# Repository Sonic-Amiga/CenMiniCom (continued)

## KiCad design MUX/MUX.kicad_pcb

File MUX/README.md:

# MUX board replica

# Modifications list.

1. SN74199 is replaced by SN74LS273

2. SN74LS154 can be replaced by russian КР1533ИД3 in a narrow package, extra row of pins provided

3. Added jumper blocks for easy switch between original Centurion and standard RS-232 output pinouts.

See git log for more verbose history

Russian characters in this file are using UTF-8 character set.

|Original   |Replacement        |Notes					|
|-----------|-------------------|---------------------------------------|
|74LS00		|К555ЛА3			|					|
|74LS02		|К555ЛЕ1			|					|
|74LS04		|К555ЛН1			|					|
|74LS08		|К555ЛИ1			|
|74LS10		|К555ЛА4			|					|
|74LS20		|К555ЛА1			|					|
|74LS30		|К555ЛА2			|					|
|SN7425		|155ЛЕ3				|
|74LS37		|К555ЛА12			|					|
|74LS38		|К555ЛА13			|					|
|74LS42		|К555ИД6			|
|74LS74		|К555ТМ2			|					|
|74LS75		|555TM7				|
|74LS85		|555СП1				|
|74LS148	|КМ555ИВ1			|
|74LS151	|К555КП7			|					|
|74LS154	|К155ИД3, К1533ИД3	| К1533 series uses narrow DIP package	|
|74LS161	|К555ИЕ10			|
|74LS195	|					|
|74LS240	|К555АП3			|					|
|74LS273	|К555ИР35			|
|74LS367	|КР571ХЛ5			|
|74LS393	|К555ИЕ19			|
|SN75150	|170АП2				|
|SN75154	|170УП2				|

# Contacts

Please direct all questions to pavel_fedin@mail.ru

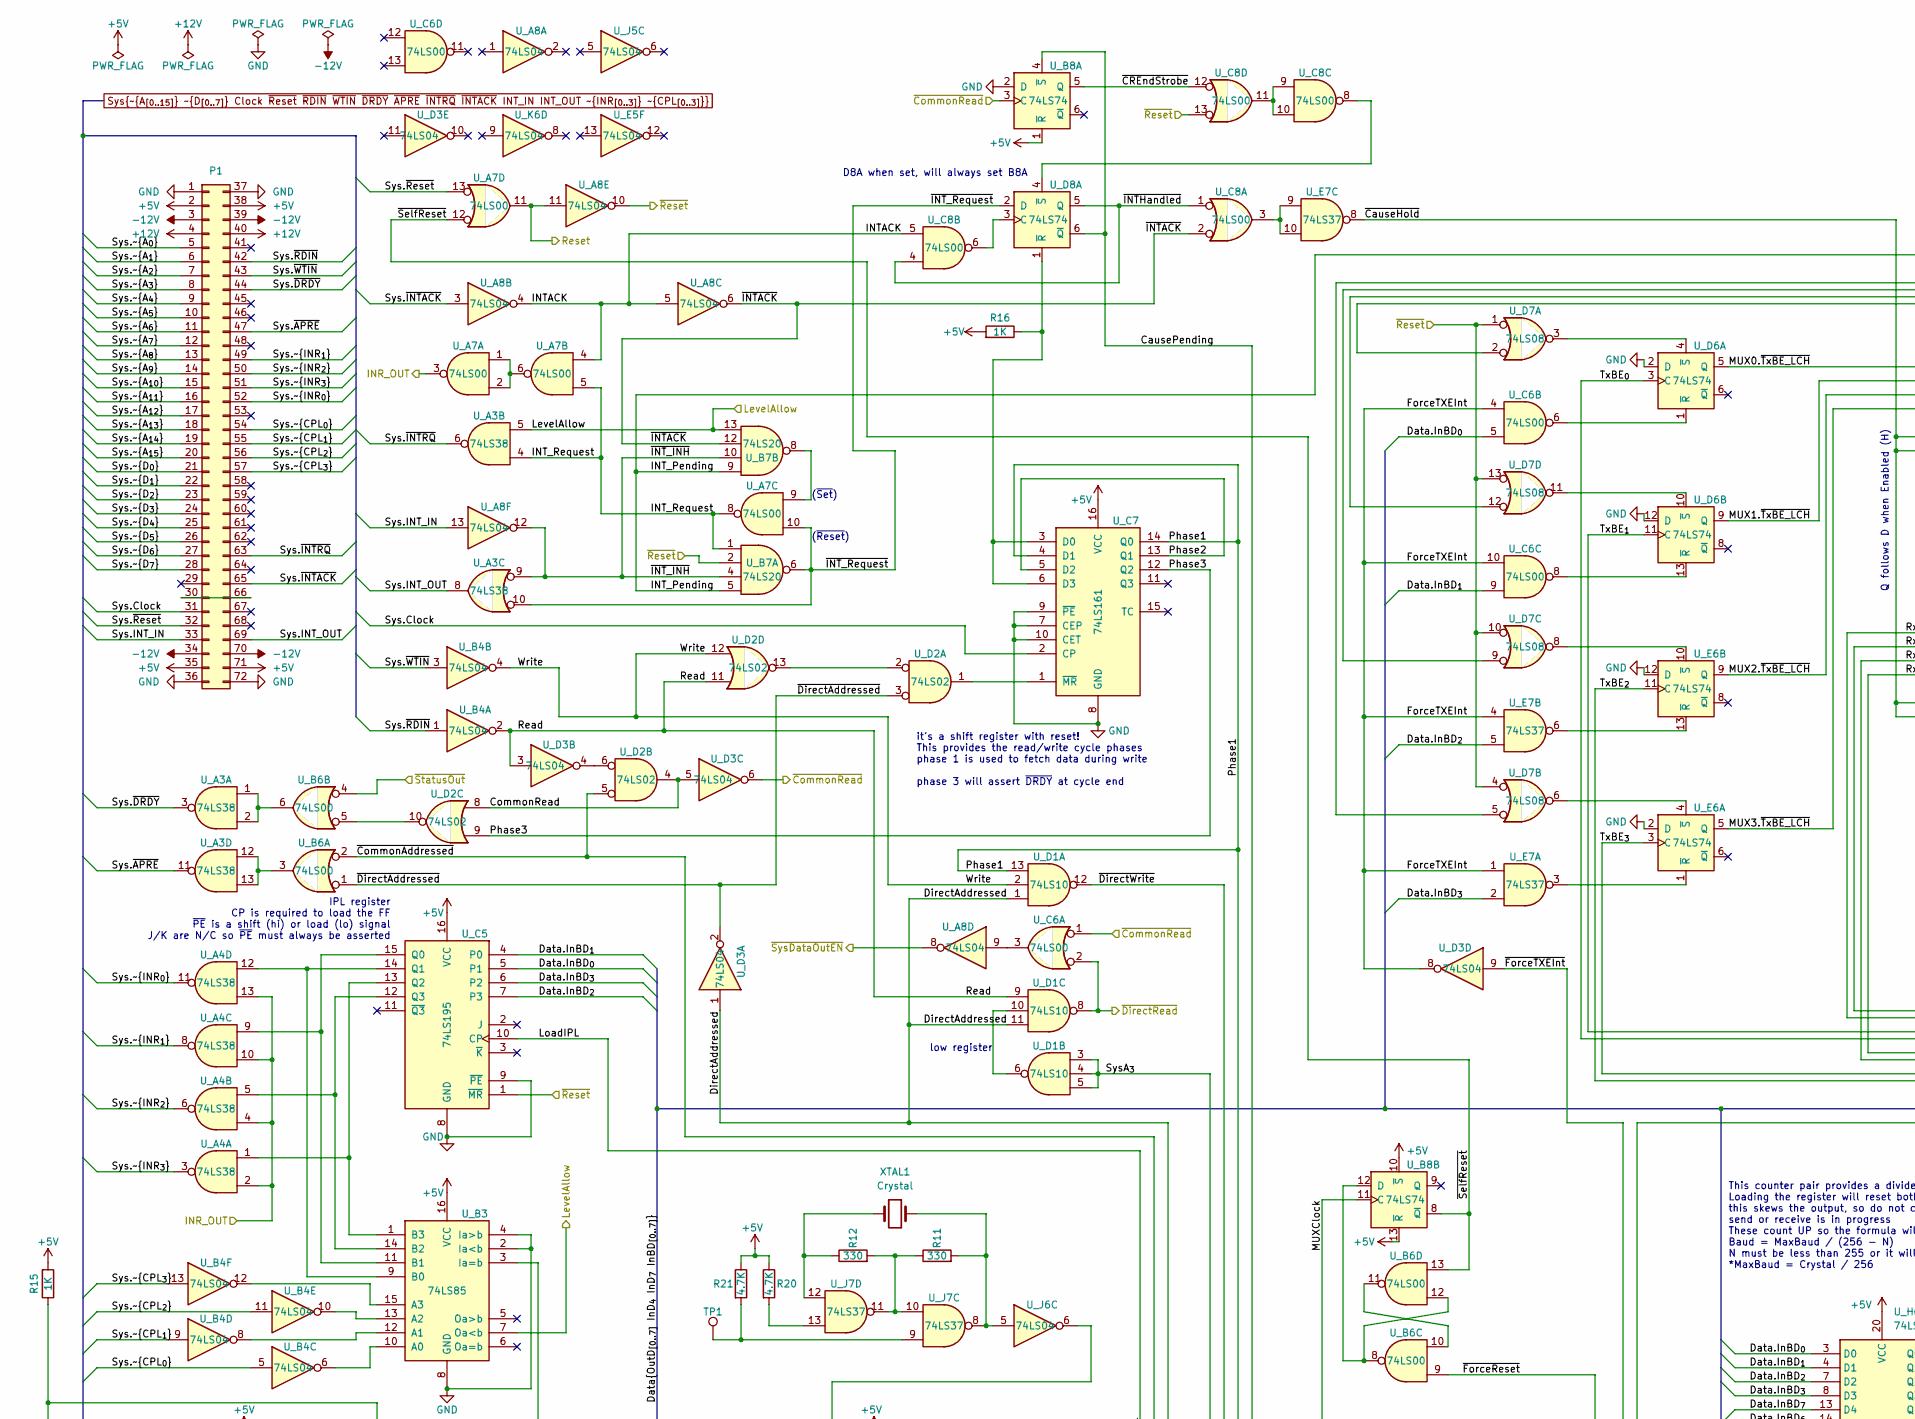
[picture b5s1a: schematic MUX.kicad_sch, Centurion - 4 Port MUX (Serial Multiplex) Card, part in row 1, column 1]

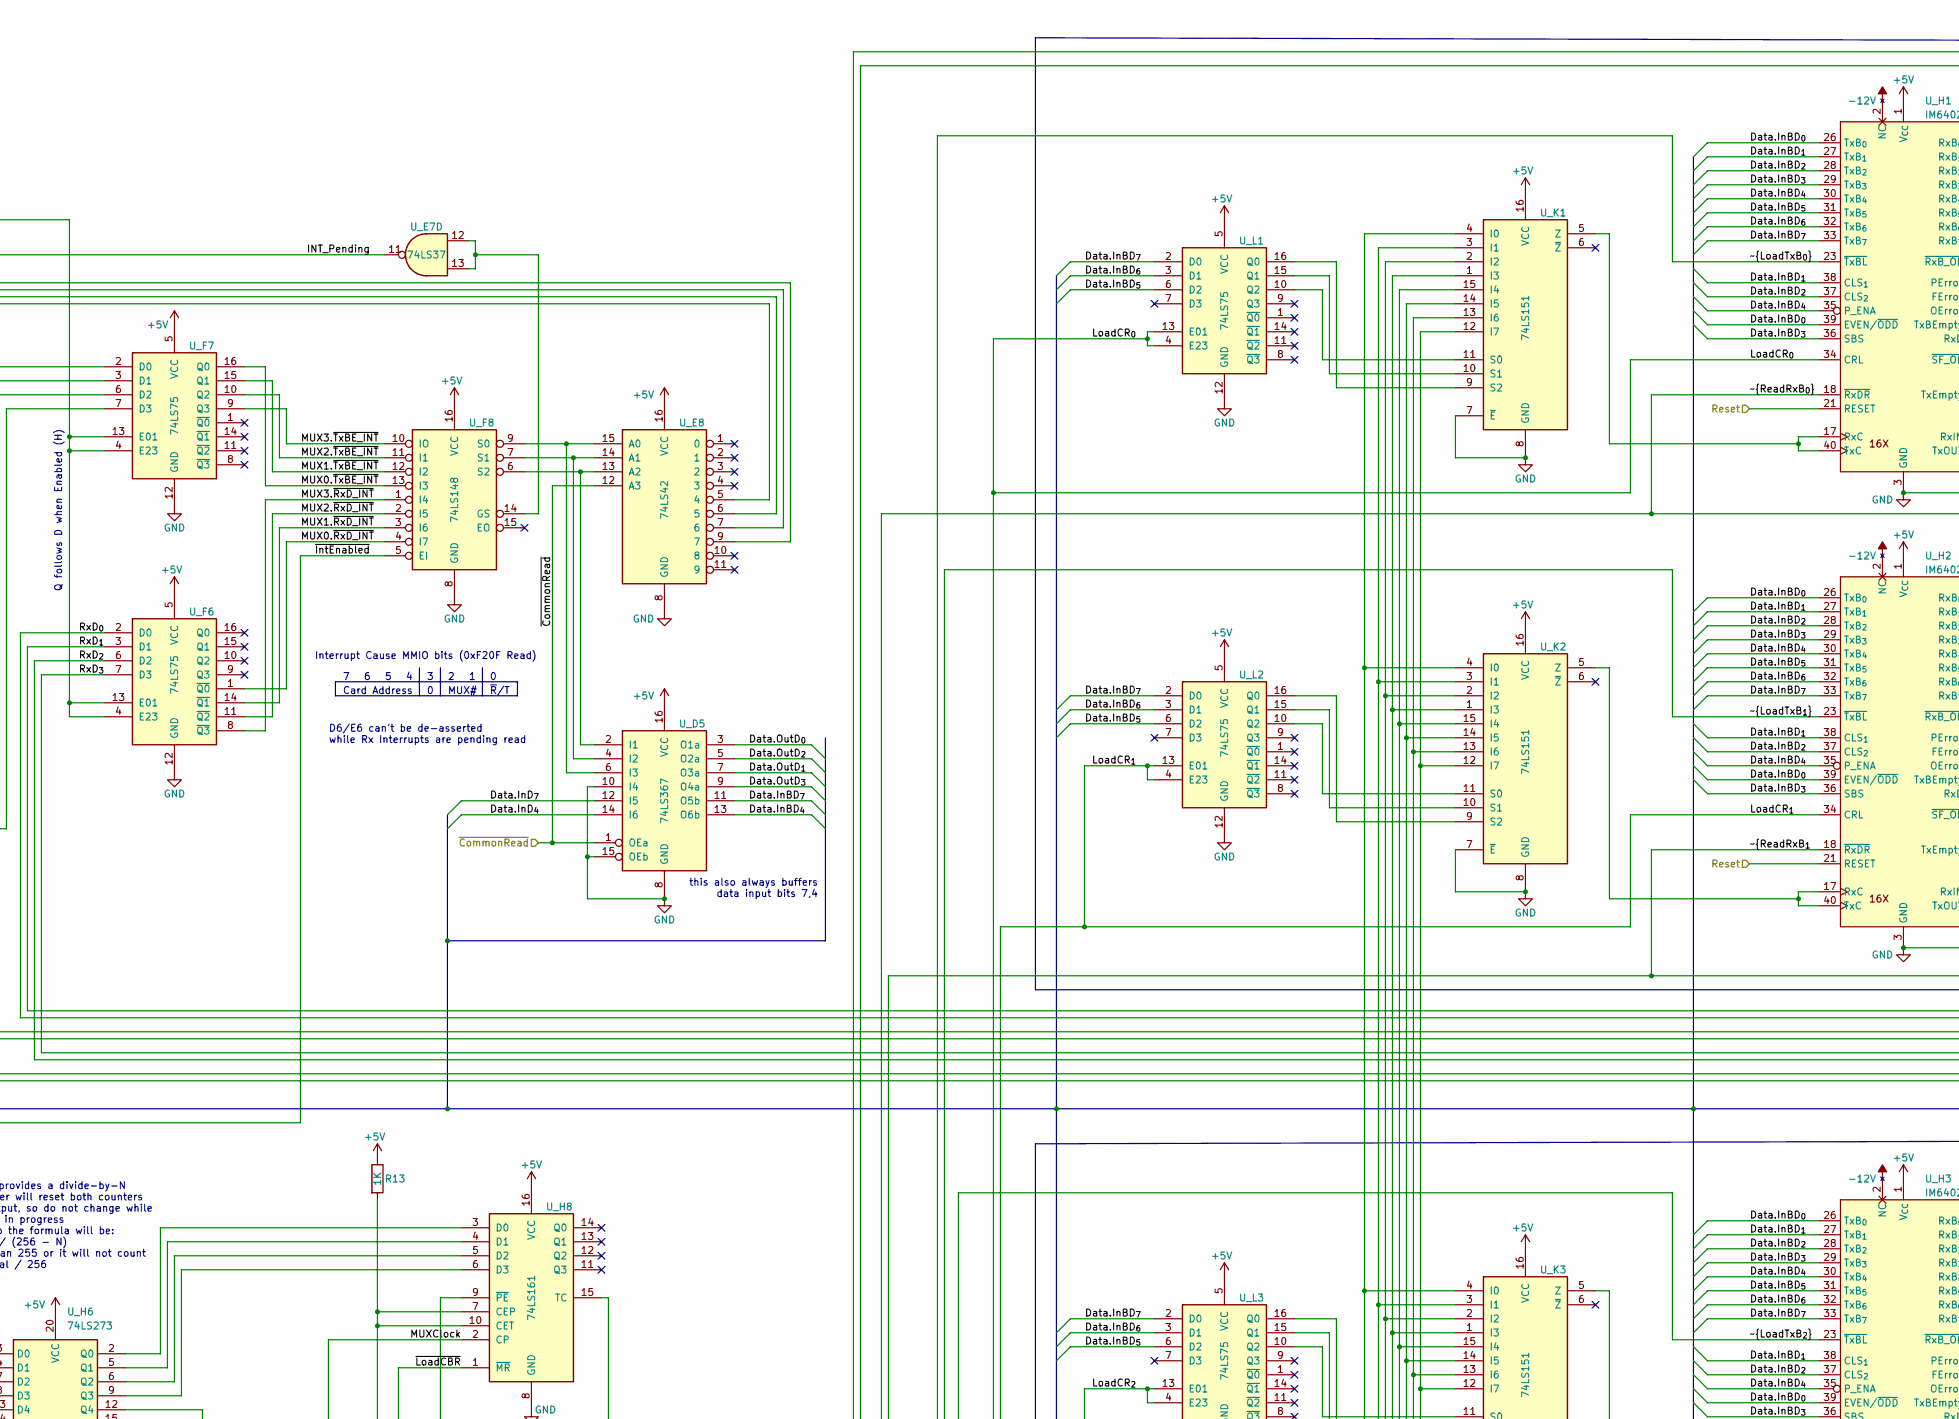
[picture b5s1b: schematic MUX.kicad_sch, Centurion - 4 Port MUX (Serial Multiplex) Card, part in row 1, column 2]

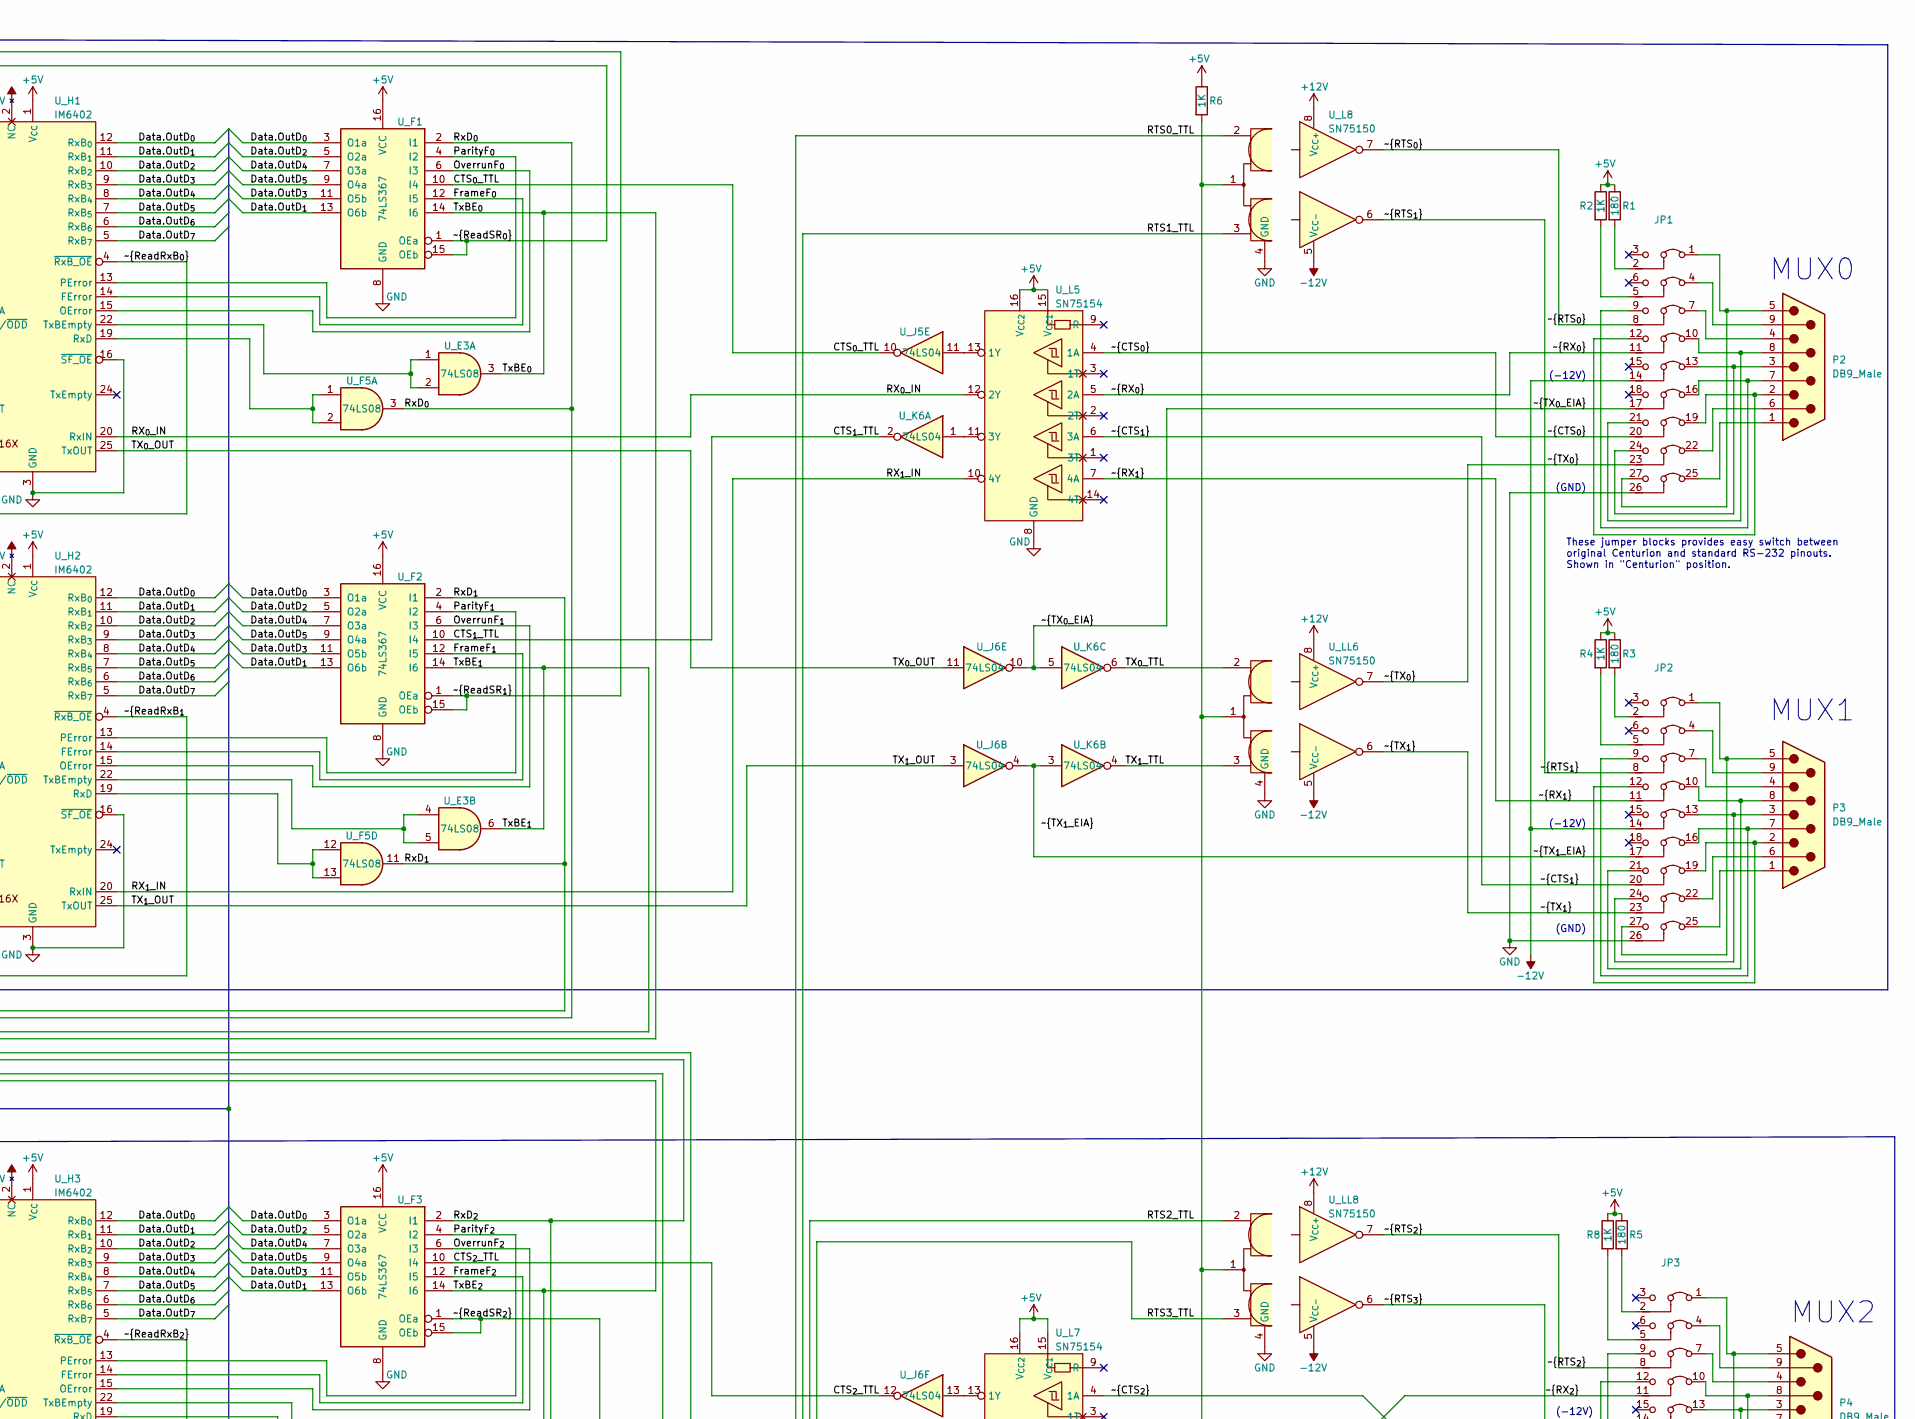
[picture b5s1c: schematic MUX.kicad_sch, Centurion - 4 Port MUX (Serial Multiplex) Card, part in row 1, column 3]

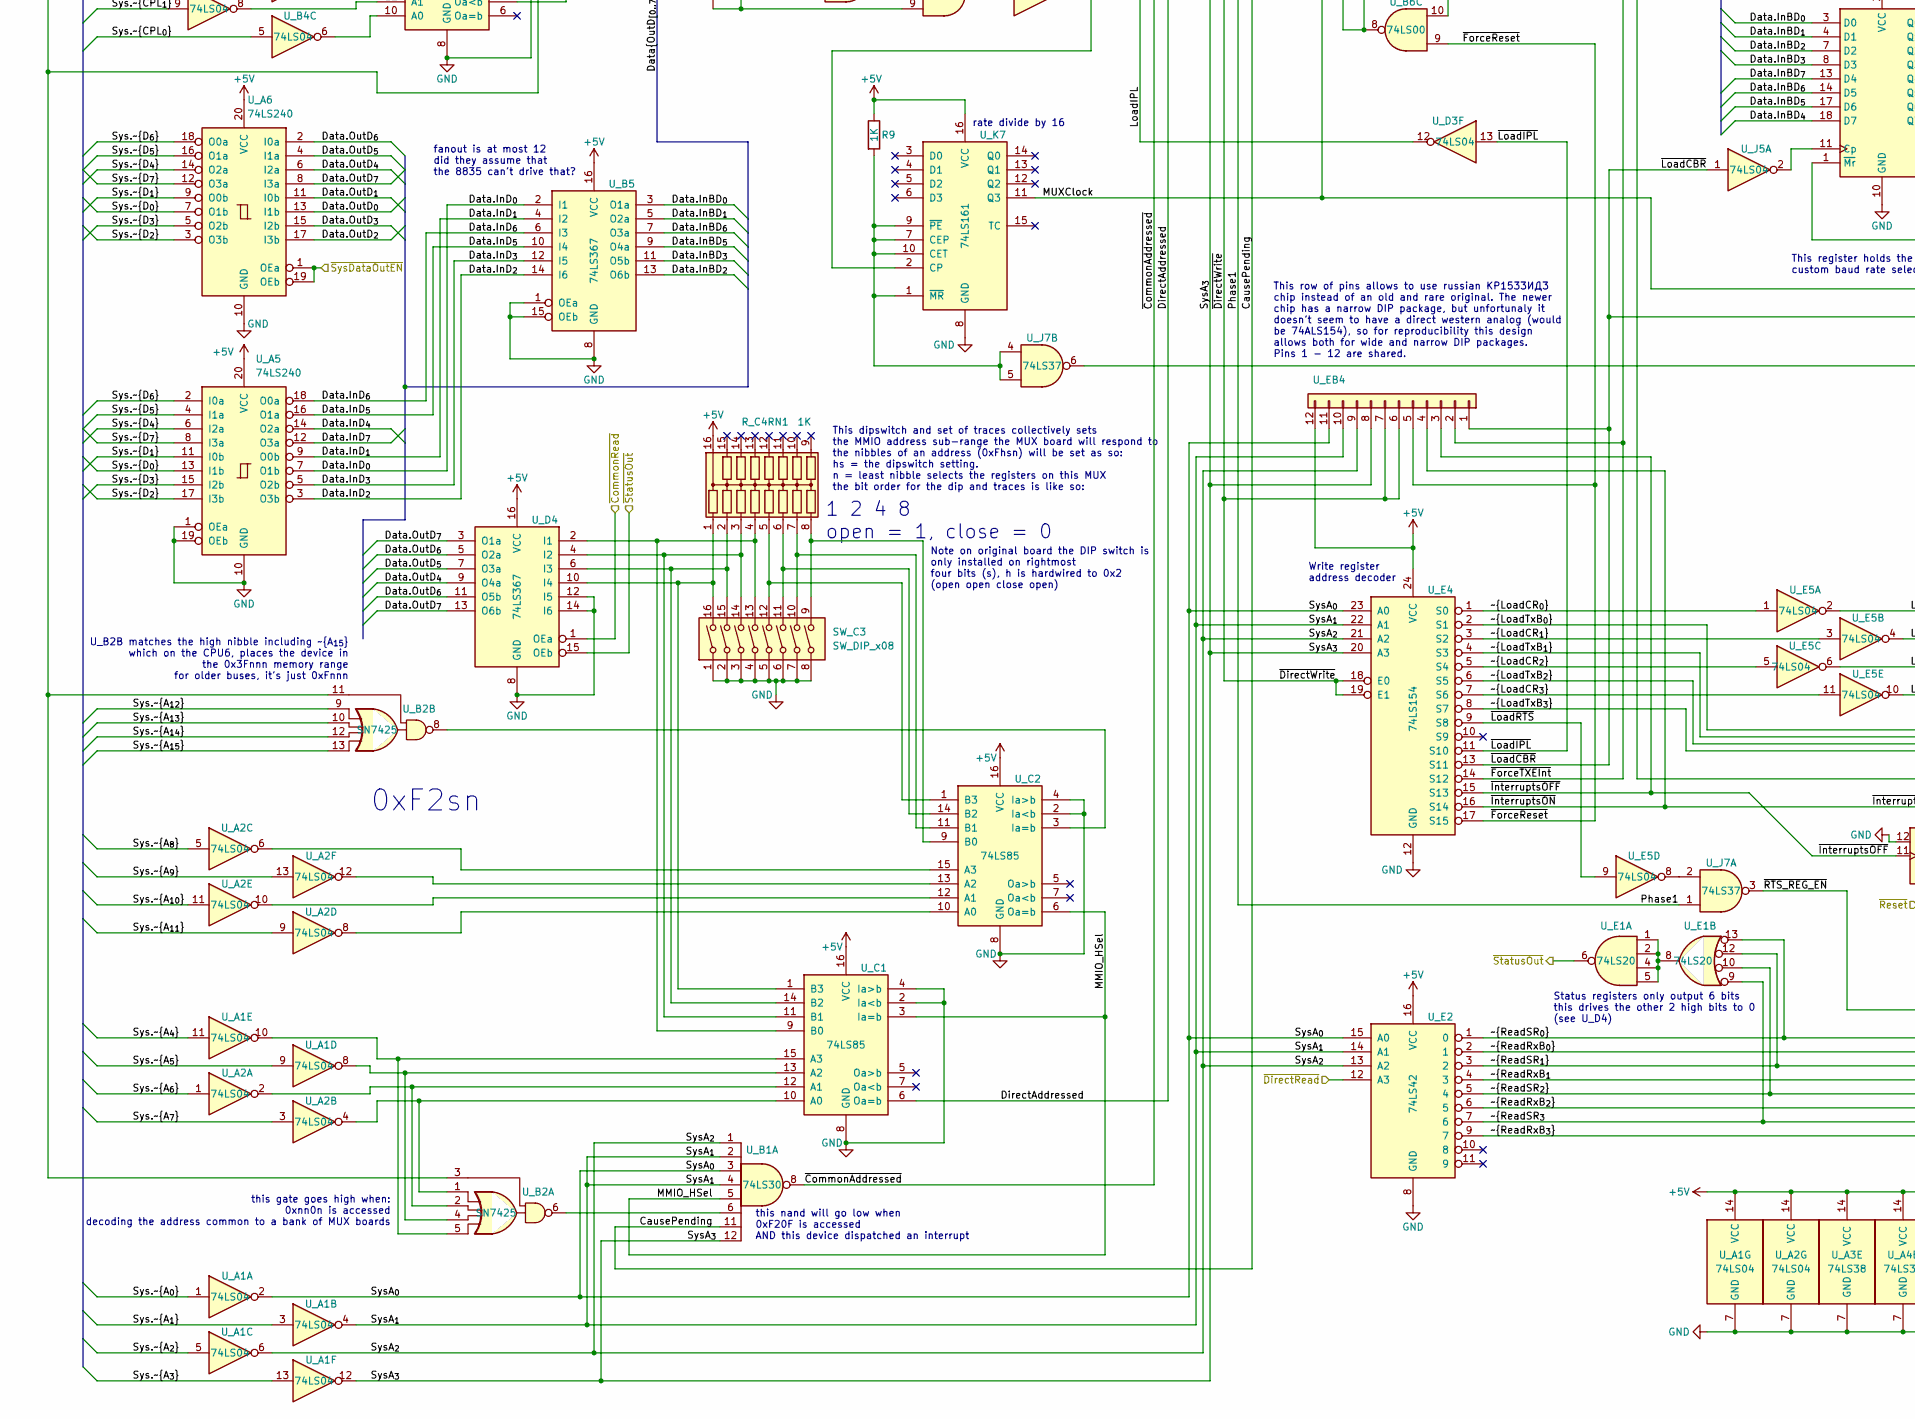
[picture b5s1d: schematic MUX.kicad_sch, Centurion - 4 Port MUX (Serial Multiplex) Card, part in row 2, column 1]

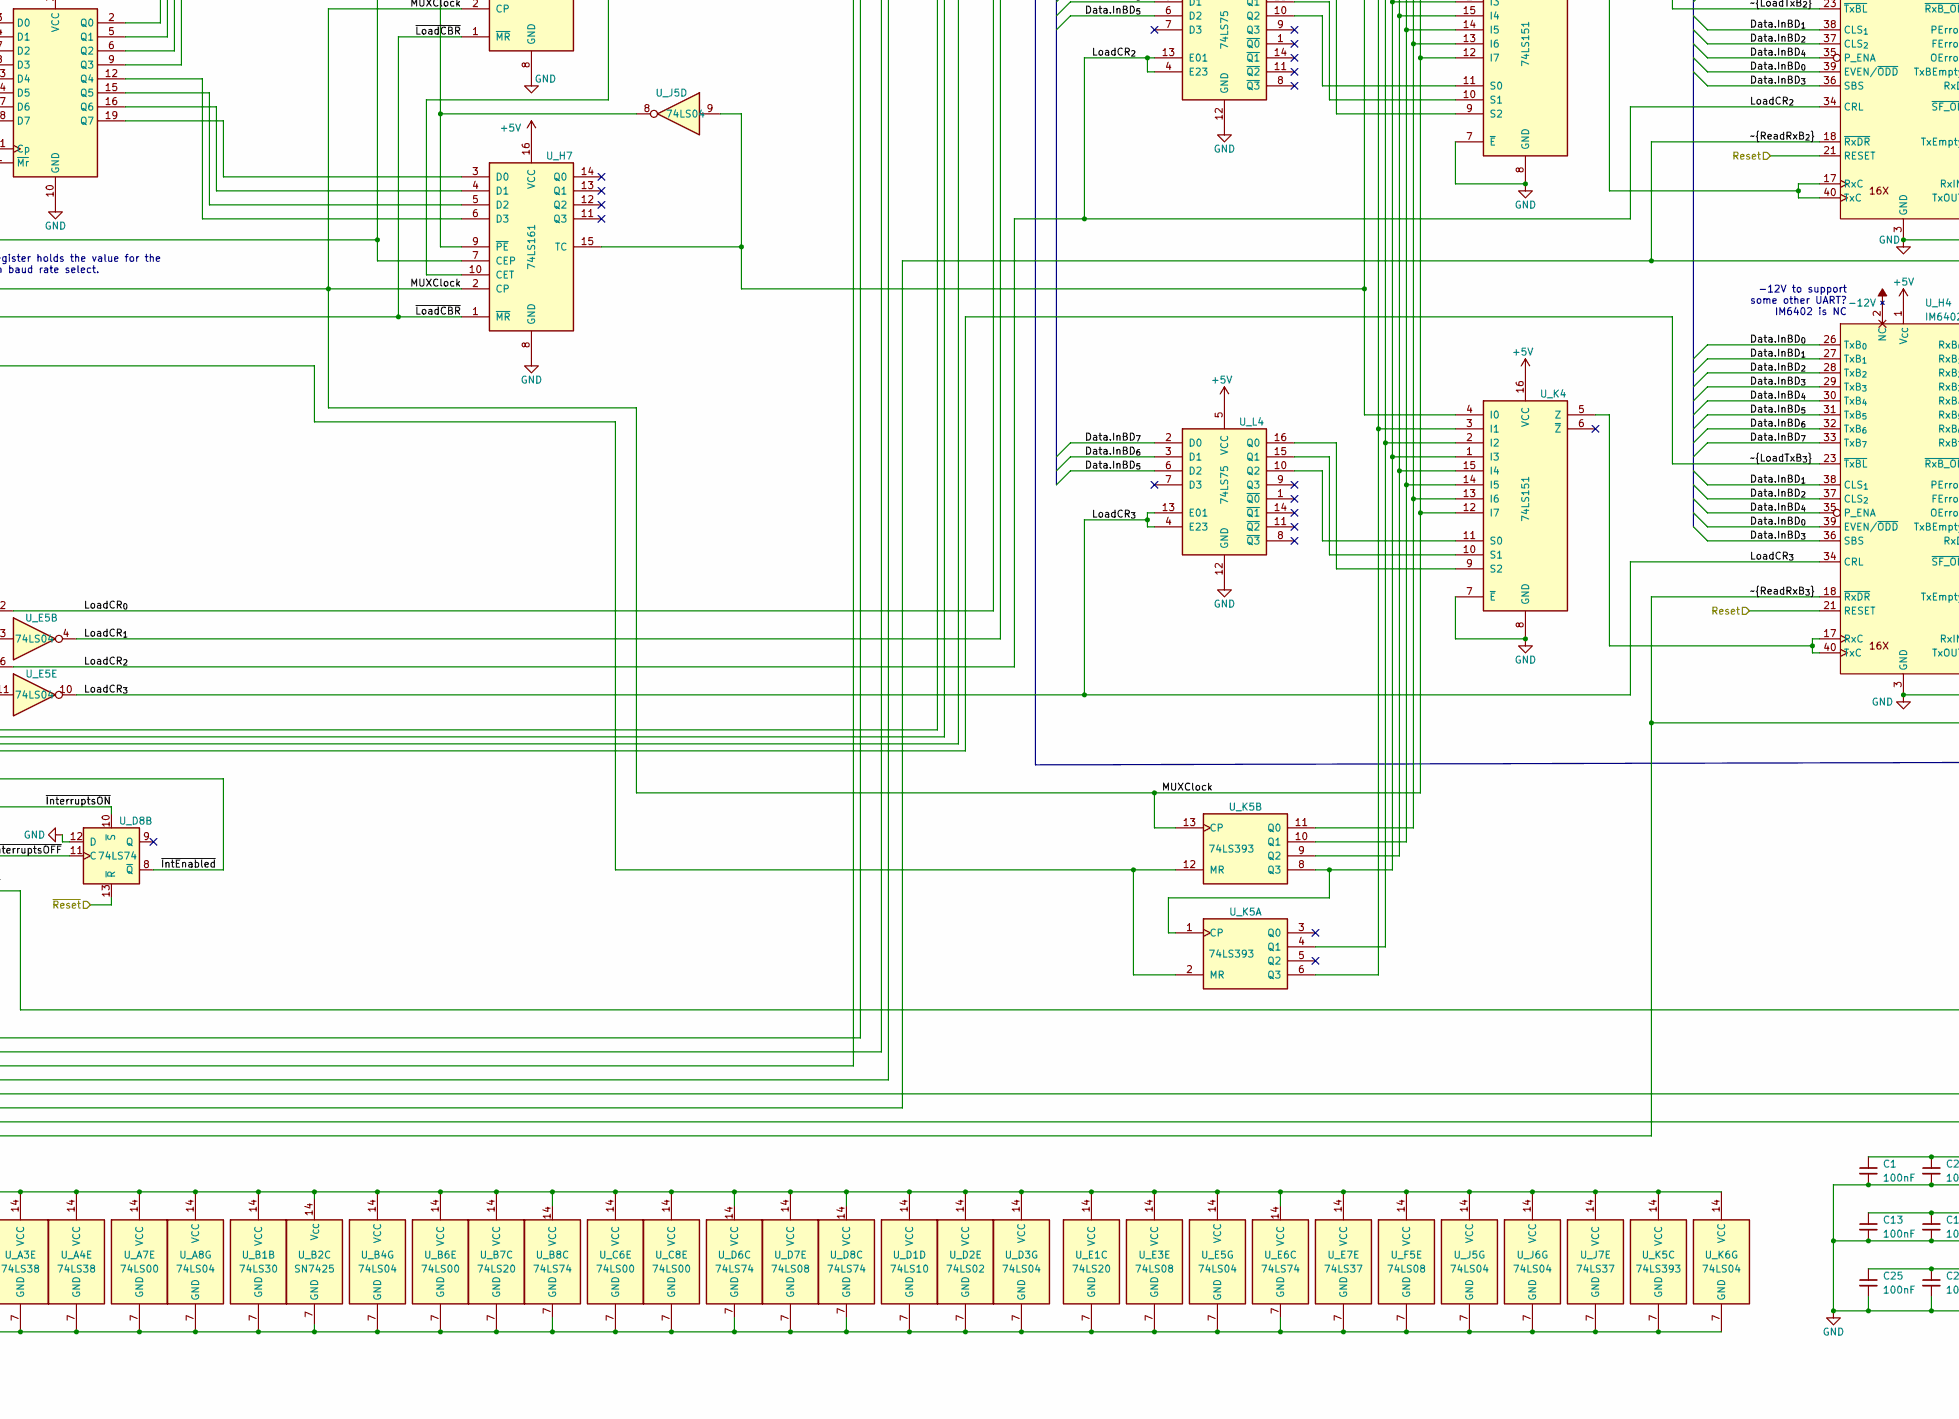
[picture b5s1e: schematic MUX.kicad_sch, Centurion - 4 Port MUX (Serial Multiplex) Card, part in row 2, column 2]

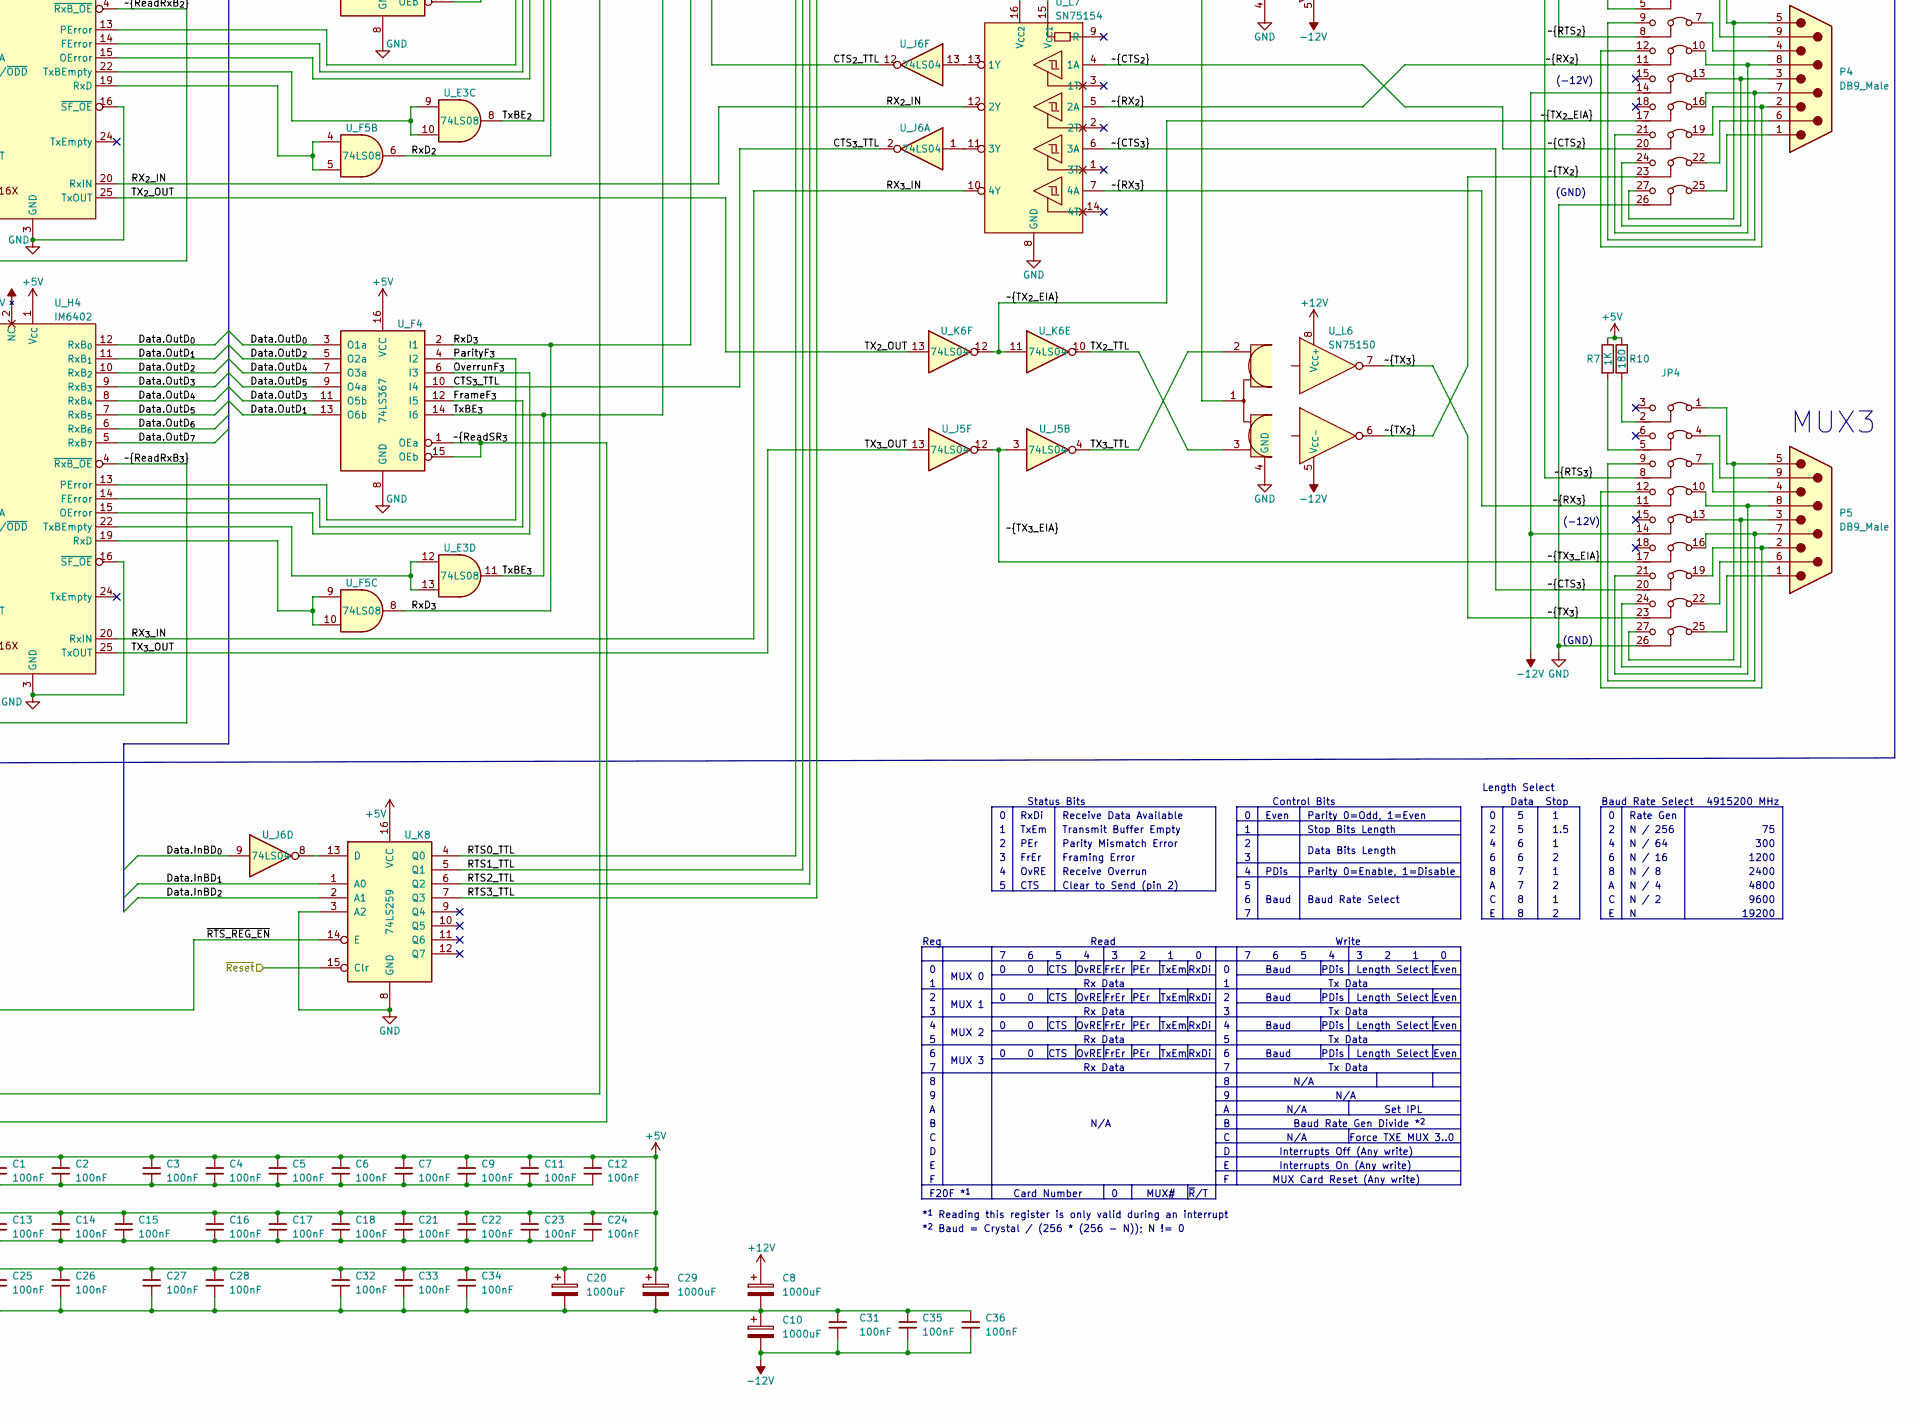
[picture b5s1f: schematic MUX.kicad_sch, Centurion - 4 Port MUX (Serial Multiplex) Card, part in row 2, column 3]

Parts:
C1, C2, C3, C4, C5, C6, C7, C9, C11, C12, C13, C14, C15, C16, C17, C18, C21, C22, C23, C24, C25, C26, C27, C28, C31, C32, C33, C34, C35, C36: 100nF; C_Disc_D4.3mm_W1.9mm_P5.00mm
C8, C10, C20, C29: 1000uF; CP_Axial_L25.0mm_D10.0mm_P30.00mm_Horizontal
JP1, JP2, JP3, JP4: Jumper_3x9_Bridged12; PinHeader_3x09_P2.54mm_Vertical
P1: Conn_02x36_Top_Bottom; BUS_EE200
P2, P3, P4, P5: DB9_Male; DSUB-9_Male_Horizontal_P2.77x2.84mm_EdgePinOffset4.94mm_Hou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
R1, R3, R5, R10: 180; R_Axial_DIN0204_L3.6mm_D1.6mm_P7.62mm_Horizontal
R2, R4, R6, R7, R8, R9, R13, R15, R16: 1K; R_Axial_DIN0204_L3.6mm_D1.6mm_P7.62mm_Horizontal
R11, R12: 330; R_Axial_DIN0204_L3.6mm_D1.6mm_P7.62mm_Horizontal
R20, R21: 4.7K; R_Axial_DIN0204_L3.6mm_D1.6mm_P7.62mm_Horizontal
R_C4RN1: 1K; DIP-16_W7.62mm
SW_C3: SW_DIP_x08; SW_DIP_SPSTx08_Slide_6.7x21.88mm_W7.62mm_P2.54mm_LowProfile
TP1: TestPoint; TestPoint_Plated_Hole_D2.0mm
U_A1, U_A2, U_A8: 74LS04; DIP-14_W7.62mm
U_A3, U_A4: 74LS38; DIP-14_W7.62mm
U_A5, U_A6: 74LS240; DIP-20_W7.62mm
U_A7: 74LS00; DIP-14_W7.62mm
U_B1: 74LS30; DIP-14_W7.62mm
U_B2: SN7425; DIP-14_W7.62mm
U_B3: 74LS85; DIP-16_W7.62mm
U_B4: 74LS04; DIP-14_W7.62mm
U_B5: 74LS367; DIP-16_W7.62mm
U_B6: 74LS00; DIP-14_W7.62mm
U_B7: 74LS20; DIP-14_W7.62mm
U_B8: 74LS74; DIP-14_W7.62mm
U_C1, U_C2: 74LS85; DIP-16_W7.62mm
U_C5: 74LS195; DIP-16_W7.62mm
U_C6, U_C8: 74LS00; DIP-14_W7.62mm
U_C7: 74LS161; DIP-16_W7.62mm
U_D1: 74LS10; DIP-14_W7.62mm
U_D2: 74LS02; DIP-14_W7.62mm
U_D3: 74LS04; DIP-14_W7.62mm
U_D4, U_D5: 74LS367; DIP-16_W7.62mm
U_D6, U_D8: 74LS74; DIP-14_W7.62mm
U_D7: 74LS08; DIP-14_W7.62mm
U_E1: 74LS20; DIP-14_W7.62mm
U_E2, U_E8: 74LS42; DIP-16_W7.62mm
U_E3: 74LS08; DIP-14_W7.62mm
U_E4: 74LS154; DIP-24_W7.62mm
U_E5: 74LS04; DIP-14_W7.62mm
U_E6: 74LS74; DIP-14_W7.62mm
U_E7: 74LS37; DIP-14_W7.62mm
U_EB4: КР1533ИД3; PinSocket_1x12_P2.54mm_Vertical
U_F1, U_F2, U_F3, U_F4: 74LS367; DIP-16_W7.62mm
U_F5: 74LS08; DIP-14_W7.62mm
U_F6, U_F7: 74LS75; DIP-16_W7.62mm
U_F8: 74LS148; DIP-16_W7.62mm
U_H1, U_H2, U_H3, U_H4: IM6402; DIP-40_W15.24mm_Socket
U_H6: 74LS273; DIP-20_W7.62mm
U_H7, U_H8: 74LS161; DIP-16_W7.62mm
U_J5, U_J6: 74LS04; DIP-14_W7.62mm
U_J7: 74LS37; DIP-14_W7.62mm
U_K1, U_K2, U_K3, U_K4: 74LS151; DIP-16_W7.62mm
U_K5: 74LS393; DIP-14_W7.62mm
U_K6: 74LS04; DIP-14_W7.62mm
U_K7: 74LS161; DIP-16_W7.62mm
U_K8: 74LS259; DIP-16_W7.62mm
U_L1, U_L2, U_L3, U_L4: 74LS75; DIP-16_W7.62mm
U_L5, U_L7: SN75154; DIP-16_W7.62mm
U_L6, U_L8: SN75150; DIP-8_W7.62mm
U_LL6, U_LL8: SN75150; DIP-8_W7.62mm
XTAL1: Crystal; Crystal_HC49-U_Horizontal

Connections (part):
+5V: C1.1, C2.1, C3.1, C4.1, C5.1, C6.1, C7.1, C9.1, C11.1, C12.1, C13.1, C14.1, C15.1, C16.1, C17.1, C18.1, C20.1, C21.1, C22.1, C23.1, C24.1, C25.1, C26.1, C27.1, C28.1, C29.1, C32.1, C33.1, C34.1, P1.2, P1.35, P1.38, P1.71, R1.1, R2.1, R3.1, R4.1, R5.1, R6.1, R7.1, R8.1, R9.1, R10.1, R13.1, R15.2, R16.2, R20.1, R21.1, R_C4RN1.16, U_A1.14 (VCC), U_A2.14 (VCC), U_A3.14 (VCC), U_A4.14 (VCC), U_A5.20 (VCC), U_A6.20 (VCC), U_A7.14 (VCC), U_A8.14 (VCC), U_B1.14 (VCC), U_B2.14 (V_{CC}), U_B3.16 (VCC), U_B4.14 (VCC), U_B5.16 (VCC), U_B6.14 (VCC), U_B7.14 (VCC), U_B8.1 (~R), U_B8.10 (~S), U_B8.13 (~R), U_B8.14 (VCC), U_C1.16 (VCC), U_C2.16 (VCC), U_C5.16 (VCC), U_C6.14 (VCC), U_C7.16 (VCC), U_C8.14 (VCC), U_D1.14 (VCC), U_D2.14 (VCC), U_D3.14 (VCC), U_D4.16 (VCC), U_D5.16 (VCC), U_D6.14 (VCC)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
+12V: C8.1, P1.4, P1.40, U_L6.8 (V_{CC+}), U_L8.8 (V_{CC+}), U_LL6.8 (V_{CC+}), U_LL8.8 (V_{CC+})
-12V: C10.2, C31.2, C35.2, C36.2, JP1.14 (C5), JP2.14 (C5), JP3.14 (C5), JP4.14 (C5), P1.3, P1.34, P1.39, P1.70, U_H1.2 (NC), U_H2.2 (NC), U_H3.2 (NC), U_H4.2 (NC), U_L6.5 (V_{CC-}), U_L8.5 (V_{CC-}), U_LL6.5 (V_{CC-}), U_LL8.5 (V_{CC-})
/CTS_{0}_TTL: U_F1.10 (I4), U_J5.10
/CTS_{1}_TTL: U_F2.10 (I4), U_K6.2
/CTS_{2}_TTL: U_F3.10 (I4), U_J6.12
/CTS_{3}_TTL: U_F4.10 (I4), U_J6.2
/CausePending: U_B1.11, U_B8.4 (~S), U_D8.6 (~Q)
/CommonRead: U_D2.4, U_D2.8, U_D3.5
/Data.InBD_{0}: U_B5.3 (O1a), U_C5.5 (P1), U_C6.5, U_H1.26 (TxB_{0}), U_H1.39 (EVEN/~ODD), U_H2.26 (TxB_{0}), U_H2.39 (EVEN/~ODD), U_H3.26 (TxB_{0}), U_H3.39 (EVEN/~ODD), U_H4.26 (TxB_{0}), U_H4.39 (EVEN/~ODD), U_H6.3 (D0), U_J6.9
/Data.InBD_{1}: U_B5.5 (O2a), U_C5.4 (P0), U_C6.9, U_H1.27 (TxB_{1}), U_H1.38 (CLS_{1}), U_H2.27 (TxB_{1}), U_H2.38 (CLS_{1}), U_H3.27 (TxB_{1}), U_H3.38 (CLS_{1}), U_H4.27 (TxB_{1}), U_H4.38 (CLS_{1}), U_H6.4 (D1), U_K8.1 (A0)
/Data.InBD_{2}: U_B5.13 (O6b), U_C5.7 (P3), U_E7.5, U_H1.28 (TxB_{2}), U_H1.37 (CLS_{2}), U_H2.28 (TxB_{2}), U_H2.37 (CLS_{2}), U_H3.28 (TxB_{2}), U_H3.37 (CLS_{2}), U_H4.28 (TxB_{2}), U_H4.37 (CLS_{2}), U_H6.7 (D2), U_K8.2 (A1)
/Data.InBD_{3}: U_B5.11 (O5b), U_C5.6 (P2), U_E7.2, U_H1.29 (TxB_{3}), U_H1.36 (SBS), U_H2.29 (TxB_{3}), U_H2.36 (SBS), U_H3.29 (TxB_{3}), U_H3.36 (SBS), U_H4.29 (TxB_{3}), U_H4.36 (SBS), U_H6.8 (D3)
/Data.InBD_{4}: U_D5.13 (O6b), U_H1.30 (TxB_{4}), U_H1.35 (P_ENA), U_H2.30 (TxB_{4}), U_H2.35 (P_ENA), U_H3.30 (TxB_{4}), U_H3.35 (P_ENA), U_H4.30 (TxB_{4}), U_H4.35 (P_ENA), U_H6.18 (D7)
/Data.InBD_{5}: U_B5.9 (O4a), U_H1.31 (TxB_{5}), U_H2.31 (TxB_{5}), U_H3.31 (TxB_{5}), U_H4.31 (TxB_{5}), U_H6.17 (D6), U_L1.6 (D2), U_L2.6 (D2), U_L3.6 (D2), U_L4.6 (D2)
/Data.InBD_{6}: U_B5.7 (O3a), U_H1.32 (TxB_{6}), U_H2.32 (TxB_{6}), U_H3.32 (TxB_{6}), U_H4.32 (TxB_{6}), U_H6.14 (D5), U_L1.3 (D1), U_L2.3 (D1), U_L3.3 (D1), U_L4.3 (D1)
/Data.InBD_{7}: U_D5.11 (O5b), U_H1.33 (TxB_{7}), U_H2.33 (TxB_{7}), U_H3.33 (TxB_{7}), U_H4.33 (TxB_{7}), U_H6.13 (D4), U_L1.2 (D0), U_L2.2 (D0), U_L3.2 (D0), U_L4.2 (D0)
/Data.InD_{0}: U_A5.7 (O1b), U_B5.2 (I1)
/Data.InD_{1}: U_A5.9 (O0b), U_B5.4 (I2)
/Data.InD_{2}: U_A5.3 (O3b), U_B5.14 (I6)
/Data.InD_{3}: U_A5.5 (O2b), U_B5.12 (I5)
/Data.InD_{4}: U_A5.14 (O2a), U_D5.14 (I6)
/Data.InD_{5}: U_A5.16 (O1a), U_B5.10 (I4)
/Data.InD_{6}: U_A5.18 (O0a), U_B5.6 (I3)
/Data.InD_{7}: U_A5.12 (O3a), U_D5.12 (I5)
/Data.OutD_{0}: U_A6.13 (I1b), U_D5.3 (O1a), U_F1.3 (O1a), U_F2.3 (O1a), U_F3.3 (O1a), U_F4.3 (O1a), U_H1.12 (RxB_{0}), U_H2.12 (RxB_{0}), U_H3.12 (RxB_{0}), U_H4.12 (RxB_{0})
/Data.OutD_{1}: U_A6.11 (I0b), U_D5.7 (O3a), U_F1.13 (O6b), U_F2.13 (O6b), U_F3.13 (O6b), U_F4.13 (O6b), U_H1.11 (RxB_{1}), U_H2.11 (RxB_{1}), U_H3.11 (RxB_{1}), U_H4.11 (RxB_{1})
/Data.OutD_{2}: U_A6.17 (I3b), U_D5.5 (O2a), U_F1.5 (O2a), U_F2.5 (O2a), U_F3.5 (O2a), U_F4.5 (O2a), U_H1.10 (RxB_{2}), U_H2.10 (RxB_{2}), U_H3.10 (RxB_{2}), U_H4.10 (RxB_{2})
/Data.OutD_{3}: U_A6.15 (I2b), U_D5.9 (O4a), U_F1.11 (O5b), U_F2.11 (O5b), U_F3.11 (O5b), U_F4.11 (O5b), U_H1.9 (RxB_{3}), U_H2.9 (RxB_{3}), U_H3.9 (RxB_{3}), U_H4.9 (RxB_{3})
/Data.OutD_{4}: U_A6.6 (I2a), U_D4.9 (O4a), U_F1.7 (O3a), U_F2.7 (O3a), U_F3.7 (O3a), U_F4.7 (O3a), U_H1.8 (RxB_{4}), U_H2.8 (RxB_{4}), U_H3.8 (RxB_{4}), U_H4.8 (RxB_{4})
/Data.OutD_{5}: U_A6.4 (I1a), U_D4.7 (O3a), U_F1.9 (O4a), U_F2.9 (O4a), U_F3.9 (O4a), U_F4.9 (O4a), U_H1.7 (RxB_{5}), U_H2.7 (RxB_{5}), U_H3.7 (RxB_{5}), U_H4.7 (RxB_{5})
/Data.OutD_{6}: U_A6.2 (I0a), U_D4.5 (O2a), U_D4.11 (O5b), U_H1.6 (RxB_{6}), U_H2.6 (RxB_{6}), U_H3.6 (RxB_{6}), U_H4.6 (RxB_{6})
/Data.OutD_{7}: U_A6.8 (I3a), U_D4.3 (O1a), U_D4.13 (O6b), U_H1.5 (RxB_{7}), U_H2.5 (RxB_{7}), U_H3.5 (RxB_{7}), U_H4.5 (RxB_{7})
/DirectAddressed: U_C1.6 (Oa=b), U_D1.1, U_D1.11, U_D3.1
/ForceTXEInt: U_C6.4, U_C6.10, U_D3.8, U_E7.1, U_E7.4
/FrameF_{0}: U_F1.12 (I5), U_H1.14 (FError)
/FrameF_{1}: U_F2.12 (I5), U_H2.14 (FError)
/FrameF_{2}: U_F3.12 (I5), U_H3.14 (FError)
/FrameF_{3}: U_F4.12 (I5), U_H4.14 (FError)
/INR_OUT: U_A4.2, U_A4.4, U_A4.10, U_A4.13, U_A7.3
/INTACK: U_A7.4, U_A8.4, U_A8.5, U_C8.5
/INT_Pending: U_B7.5, U_B7.9, U_E7.11
/INT_Request: U_A3.4, U_A7.5, U_A7.8, U_B7.1
/LevelAllow: U_A3.5, U_B3.7 (Oa<b), U_B7.13
/LoadCR_{0}: U_E5.2, U_H1.34 (CRL), U_L1.4 (E23), U_L1.13 (E01)
/LoadCR_{1}: U_E5.4, U_H2.34 (CRL), U_L2.4 (E23), U_L2.13 (E01)
/LoadCR_{2}: U_E5.6, U_H3.34 (CRL), U_L3.4 (E23), U_L3.13 (E01)
/LoadCR_{3}: U_E5.10, U_H4.34 (CRL), U_L4.4 (E23), U_L4.13 (E01)
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
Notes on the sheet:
N/A
(~{Reset})
Length Select
FrEr
N / 256
Tx Data
(-12V)
(GND)
Card Address
Rx Data
This row of pins allows to use russian КР1533ИД3 chip instead of an old and rare original. The newer chip has a narrow DIP package, but unfortunaly it doesn't seem to have a direct western analog (would be 74ALS154), so for reproducibility this design allows both for wide and narrow DIP packages. P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
300
Force TXE MUX 3..0
PDis
MUX#
this gate goes high when: 0xnn0n is accessed decoding the address common to a bank of MUX boards
~{R}/T
MUX 3
MUX 0
These jumper blocks provides easy switch between original Centurion and standard RS-232 pinouts. Shown in "Centurion" position.
CTS
Interrupts On (Any write)
Baud Rate Select
Baud
this also always buffers data input bits 7,4
D6/E6 can't be de-asserted while Rx Interrupts are pending read
Even
This register holds the value for the custom baud rate select.
RxDi
IPL register CP is required to load the FF ~{PE} is a shift (hi) or load (lo) signal J/K are N/C so ~{PE} must always be asserted
TxEm
F20F *^{1}
MUX1
PEr
N / 2
U_B2B matches the high nibble including ~{A_{15}} which on the CPU6, places the device in the 0x3Fnnn memory range for older buses, it's just 0xFnnn
Receive Overrun
N / 16
OvRE
Data Bits Length

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
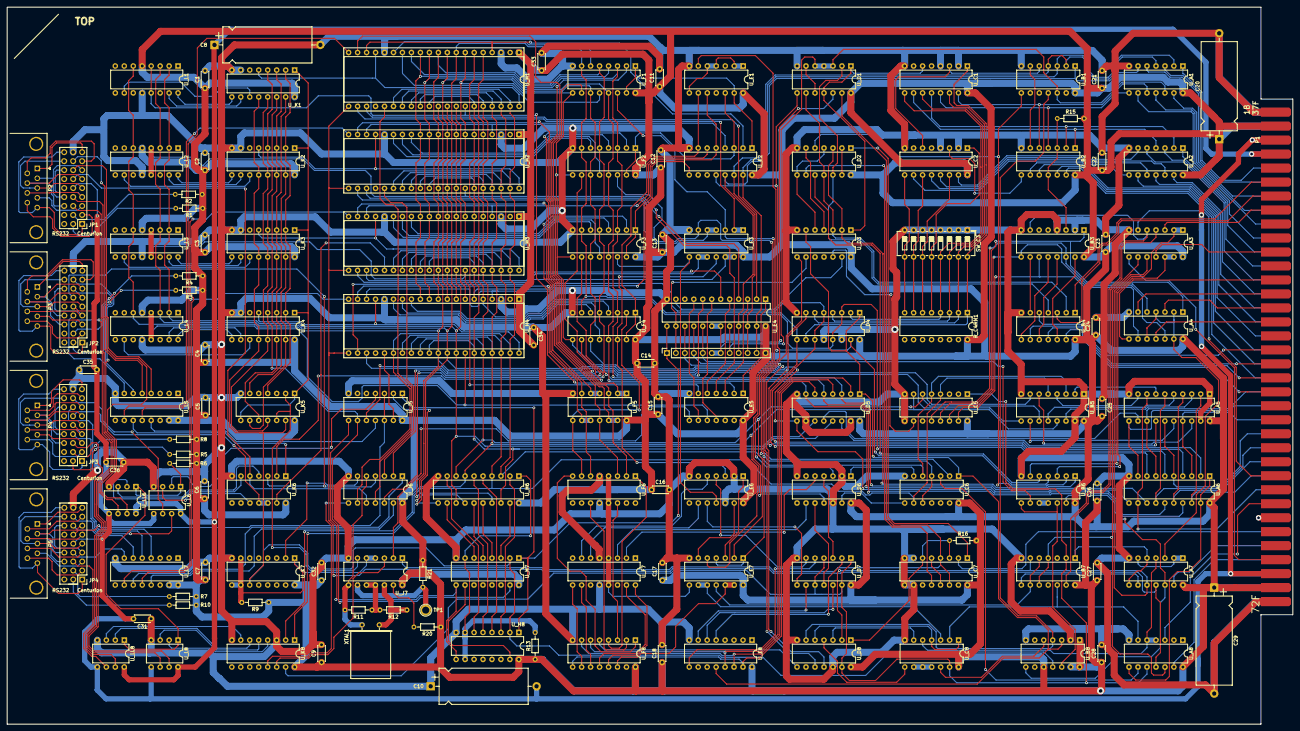
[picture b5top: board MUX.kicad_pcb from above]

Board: 4 copper layers, 364.0 x 203.0 mm, 139 parts (0 on the bottom side), 372 nets.
